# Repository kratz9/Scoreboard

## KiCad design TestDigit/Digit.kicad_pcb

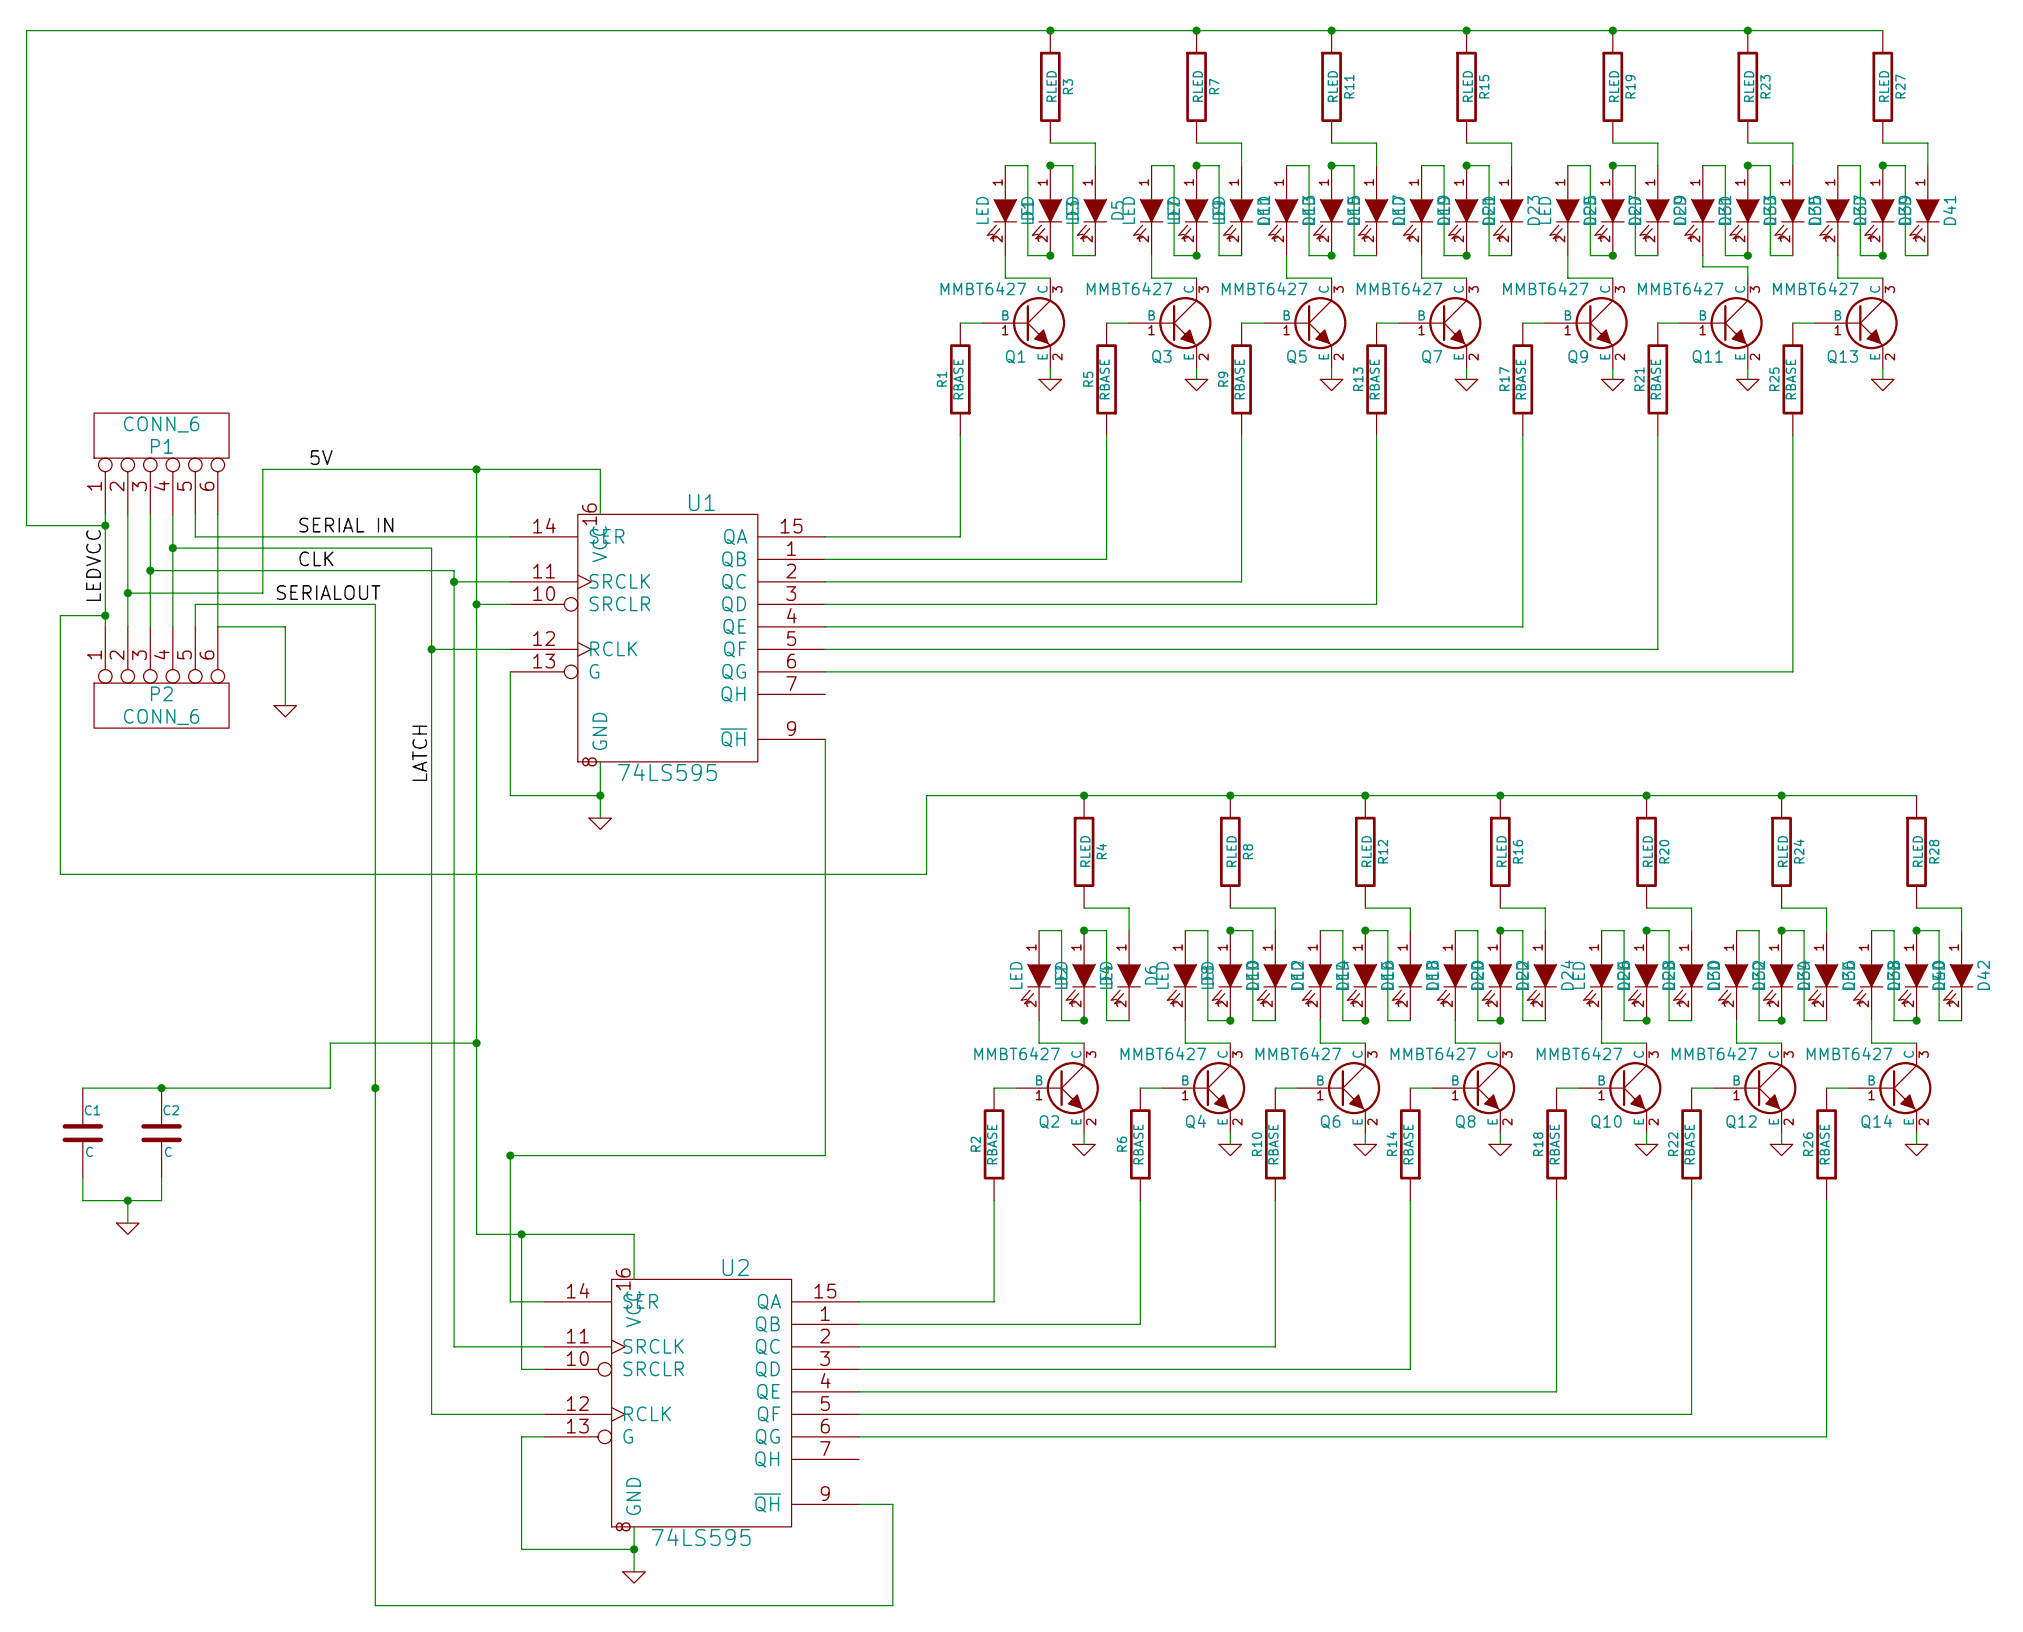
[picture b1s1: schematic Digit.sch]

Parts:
C1, C2: C
D1, D2, D3, D4, D5, D6, D7, D8, D9, D10, D11, D12, D13, D14, D15, D16, D17, D18, D19, D20, D21, D22, D23, D24, D25, D26, D27, D28, D29, D30, D31, D32, D33, D34, D35, D36, D37, D38, D39, D40, D41, D42: LED
P1, P2: CONN_6
Q1, Q2, Q3, Q4, Q5, Q6, Q7, Q8, Q9, Q10, Q11, Q12, Q13, Q14: MMBT6427
R1, R2, R5, R6, R9, R10, R13, R14, R17, R18, R21, R22, R25, R26: RBASE
R3, R4, R7, R8, R11, R12, R15, R16, R19, R20, R23, R24, R27, R28: RLED
U1, U2: 74LS595

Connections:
/5V: C1.1, C2.1, P1.2, P2.2, U1.10 (SRCLR), U1.16 (VCC), U2.10 (SRCLR), U2.16 (VCC)
/CLK: P1.3, P2.3, U1.11 (SRCLK), U2.11 (SRCLK)
/LATCH: P1.4, P2.4, U1.12 (RCLK), U2.12 (RCLK)
/LEDVCC: P1.1, P2.1, R3.1, R4.1, R7.1, R8.1, R11.1, R12.1, R15.1, R16.1, R19.1, R20.1, R23.1, R24.1, R27.1, R28.1
/SERIAL IN: P1.5, U1.14 (SER)
/SERIALOUT: P2.5, U2.9 (~QH)
GND: C1.2, C2.2, P1.6, P2.6, Q1.2 (E), Q2.2 (E), Q3.2 (E), Q4.2 (E), Q5.2 (E), Q6.2 (E), Q7.2 (E), Q8.2 (E), Q9.2 (E), Q10.2 (E), Q11.2 (E), Q12.2 (E), Q13.2 (E), Q14.2 (E), U1.8 (GND), U1.13 (G), U2.8 (GND), U2.13 (G)
unnamed: U1.9 (~QH), U2.14 (SER)
unnamed: D33.1 (A), D35.2 (K)
unnamed: D39.1 (A), D41.2 (K)
unnamed: Q2.1 (B), R2.2
unnamed: Q4.1 (B), R6.2
unnamed: Q6.1 (B), R10.2
unnamed: Q8.1 (B), R14.2
unnamed: D3.1 (A), D5.2 (K)
unnamed: R13.1, U1.3 (QD)
unnamed: R17.1, U1.4 (QE)
unnamed: R21.1, U1.5 (QF)
unnamed: R25.1, U1.6 (QG)
unnamed: Q10.1 (B), R18.2
unnamed: D7.1 (A), D9.2 (K)
unnamed: D9.1 (A), D11.2 (K)
unnamed: D15.1 (A), D17.2 (K)
unnamed: D21.1 (A), D23.2 (K)
unnamed: D27.1 (A), D29.2 (K)
unnamed: D16.1 (A), D18.2 (K)
unnamed: D22.1 (A), D24.2 (K)
unnamed: R26.1, U2.6 (QG)
unnamed: D28.1 (A), D30.2 (K)
unnamed: D34.1 (A), D36.2 (K)
unnamed: D40.1 (A), D42.2 (K)
unnamed: R10.1, U2.2 (QC)
unnamed: Q12.1 (B), R22.2
unnamed: Q14.1 (B), R26.2
unnamed: R2.1, U2.15 (QA)
unnamed: R6.1, U2.1 (QB)
unnamed: R14.1, U2.3 (QD)
unnamed: R18.1, U2.4 (QE)
unnamed: R22.1, U2.5 (QF)
unnamed: D10.1 (A), D12.2 (K)
unnamed: D12.1 (A), R8.2
unnamed: D14.2 (K), Q6.3 (C)
unnamed: D14.1 (A), D16.2 (K)
unnamed: D18.1 (A), R12.2
unnamed: D20.2 (K), Q8.3 (C)
unnamed: D20.1 (A), D22.2 (K)
unnamed: D4.1 (A), D6.2 (K)
unnamed: D41.1 (A), R27.2
unnamed: D2.2 (K), Q2.3 (C)
unnamed: D2.1 (A), D4.2 (K)
unnamed: D6.1 (A), R4.2
unnamed: D8.2 (K), Q4.3 (C)
unnamed: D8.1 (A), D10.2 (K)
unnamed: D38.2 (K), Q14.3 (C)
unnamed: D32.1 (A), D34.2 (K)
unnamed: D36.1 (A), R24.2
unnamed: D38.1 (A), D40.2 (K)
unnamed: D42.1 (A), R28.2
unnamed: D26.1 (A), D28.2 (K)
unnamed: D24.1 (A), R16.2
unnamed: D26.2 (K), Q10.3 (C)
unnamed: D30.1 (A), R20.2
unnamed: D32.2 (K), Q12.3 (C)
unnamed: D13.1 (A), D15.2 (K)
unnamed: D11.1 (A), R7.2
unnamed: D13.2 (K), Q5.3 (C)
unnamed: D17.1 (A), R11.2
unnamed: D19.2 (K), Q7.3 (C)
unnamed: D1.2 (K), Q1.3 (C)
unnamed: D1.1 (A), D3.2 (K)
unnamed: D19.1 (A), D21.2 (K)
unnamed: D5.1 (A), R3.2
unnamed: D7.2 (K), Q3.3 (C)
unnamed: D35.1 (A), R23.2
unnamed: D31.2 (K), Q11.3 (C)
unnamed: D31.1 (A), D33.2 (K)
unnamed: D37.2 (K), Q13.3 (C)
unnamed: D37.1 (A), D39.2 (K)
unnamed: D25.2 (K), Q9.3 (C)
unnamed: D23.1 (A), R15.2
unnamed: D25.1 (A), D27.2 (K)
unnamed: D29.1 (A), R19.2
unnamed: Q3.1 (B), R5.2
unnamed: Q5.1 (B), R9.2
unnamed: R9.1, U1.2 (QC)
unnamed: R1.1, U1.15 (QA)
unnamed: Q1.1 (B), R1.2
unnamed: Q13.1 (B), R25.2
unnamed: Q7.1 (B), R13.2
unnamed: Q9.1 (B), R17.2
unnamed: Q11.1 (B), R21.2
unnamed: R5.1, U1.1 (QB)

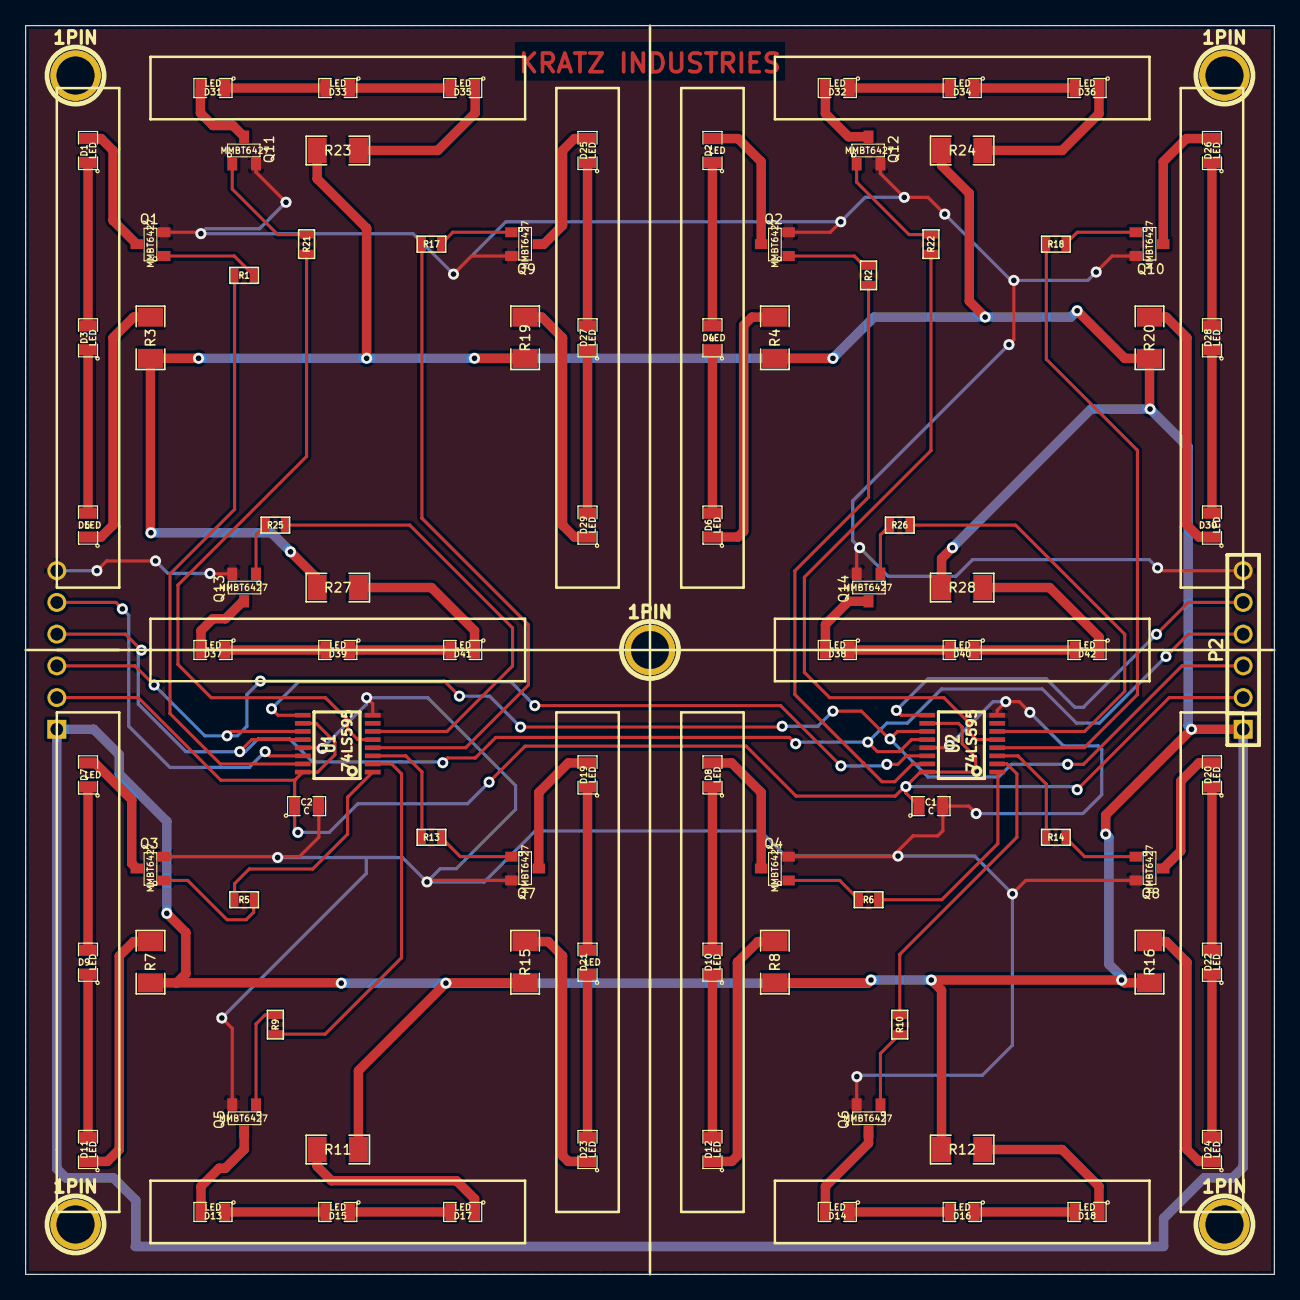
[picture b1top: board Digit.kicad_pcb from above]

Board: 2 copper layers, 100.0 x 100.0 mm, 95 parts (1 on the bottom side), 92 nets.

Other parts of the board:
1PIN, 1PIN#2, 1PIN#3, 1PIN#4, 1PIN#5: P***; 1pin

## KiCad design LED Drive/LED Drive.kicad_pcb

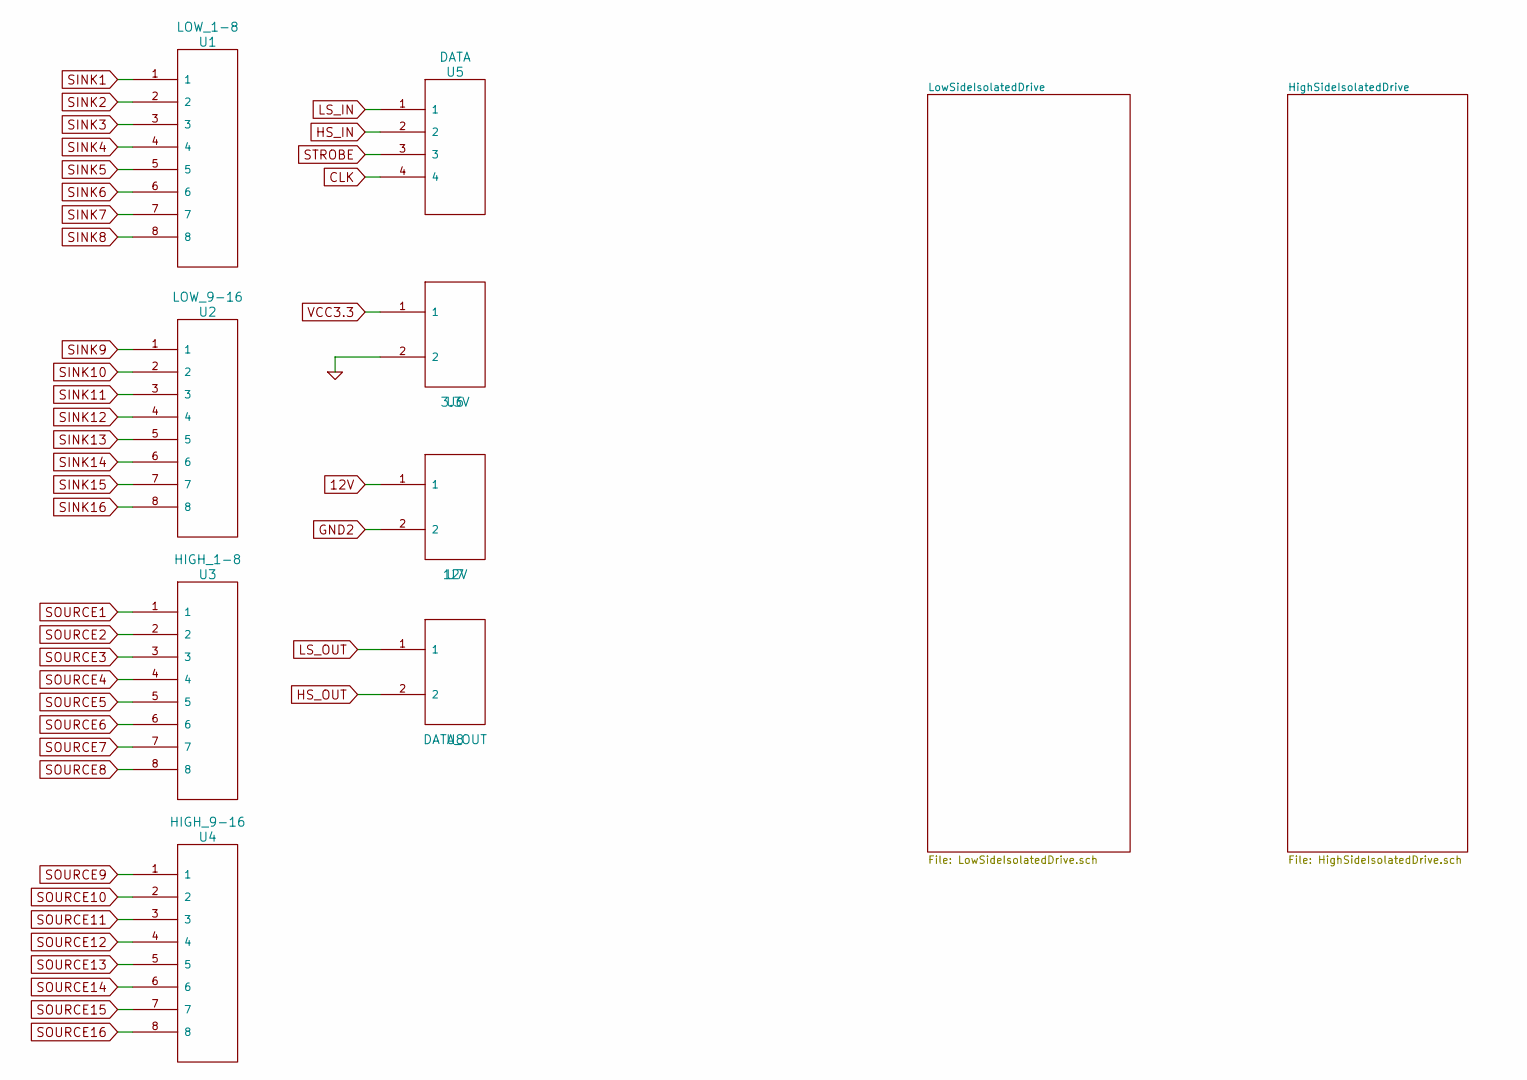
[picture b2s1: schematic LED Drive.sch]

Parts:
U1: LOW_1-8
U2: LOW_9-16
U3: HIGH_1-8
U4: HIGH_9-16
U5: DATA
U6: 3.3V
U7: 12V
U8: DATA_OUT

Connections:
12V: U7.1; also elsewhere on the board
CLK: U5.4; also elsewhere on the board
GND: U6.2; also elsewhere on the board
GND2: U7.2; also elsewhere on the board
HS_IN: U5.2; also elsewhere on the board
HS_OUT: U8.2; also elsewhere on the board
LS_IN: U5.1; also elsewhere on the board
LS_OUT: U8.1; also elsewhere on the board
SINK1: U1.1; also elsewhere on the board
SINK2: U1.2; also elsewhere on the board
SINK3: U1.3; also elsewhere on the board
SINK4: U1.4; also elsewhere on the board
SINK5: U1.5; also elsewhere on the board
SINK6: U1.6; also elsewhere on the board
SINK7: U1.7; also elsewhere on the board
SINK8: U1.8; also elsewhere on the board
SINK9: U2.1; also elsewhere on the board
SINK10: U2.2; also elsewhere on the board
SINK11: U2.3; also elsewhere on the board
SINK12: U2.4; also elsewhere on the board
SINK13: U2.5; also elsewhere on the board
SINK14: U2.6; also elsewhere on the board
SINK15: U2.7; also elsewhere on the board
SINK16: U2.8; also elsewhere on the board
SOURCE1: U3.1; also elsewhere on the board
SOURCE2: U3.2; also elsewhere on the board
SOURCE3: U3.3; also elsewhere on the board
SOURCE4: U3.4; also elsewhere on the board
SOURCE5: U3.5; also elsewhere on the board
SOURCE6: U3.6; also elsewhere on the board
SOURCE7: U3.7; also elsewhere on the board
SOURCE8: U3.8; also elsewhere on the board
SOURCE9: U4.1; also elsewhere on the board
SOURCE10: U4.2; also elsewhere on the board
SOURCE11: U4.3; also elsewhere on the board
SOURCE12: U4.4; also elsewhere on the board
SOURCE13: U4.5; also elsewhere on the board
SOURCE14: U4.6; also elsewhere on the board
SOURCE15: U4.7; also elsewhere on the board
SOURCE16: U4.8; also elsewhere on the board
STROBE: U5.3; also elsewhere on the board
VCC3.3: U6.1; also elsewhere on the board

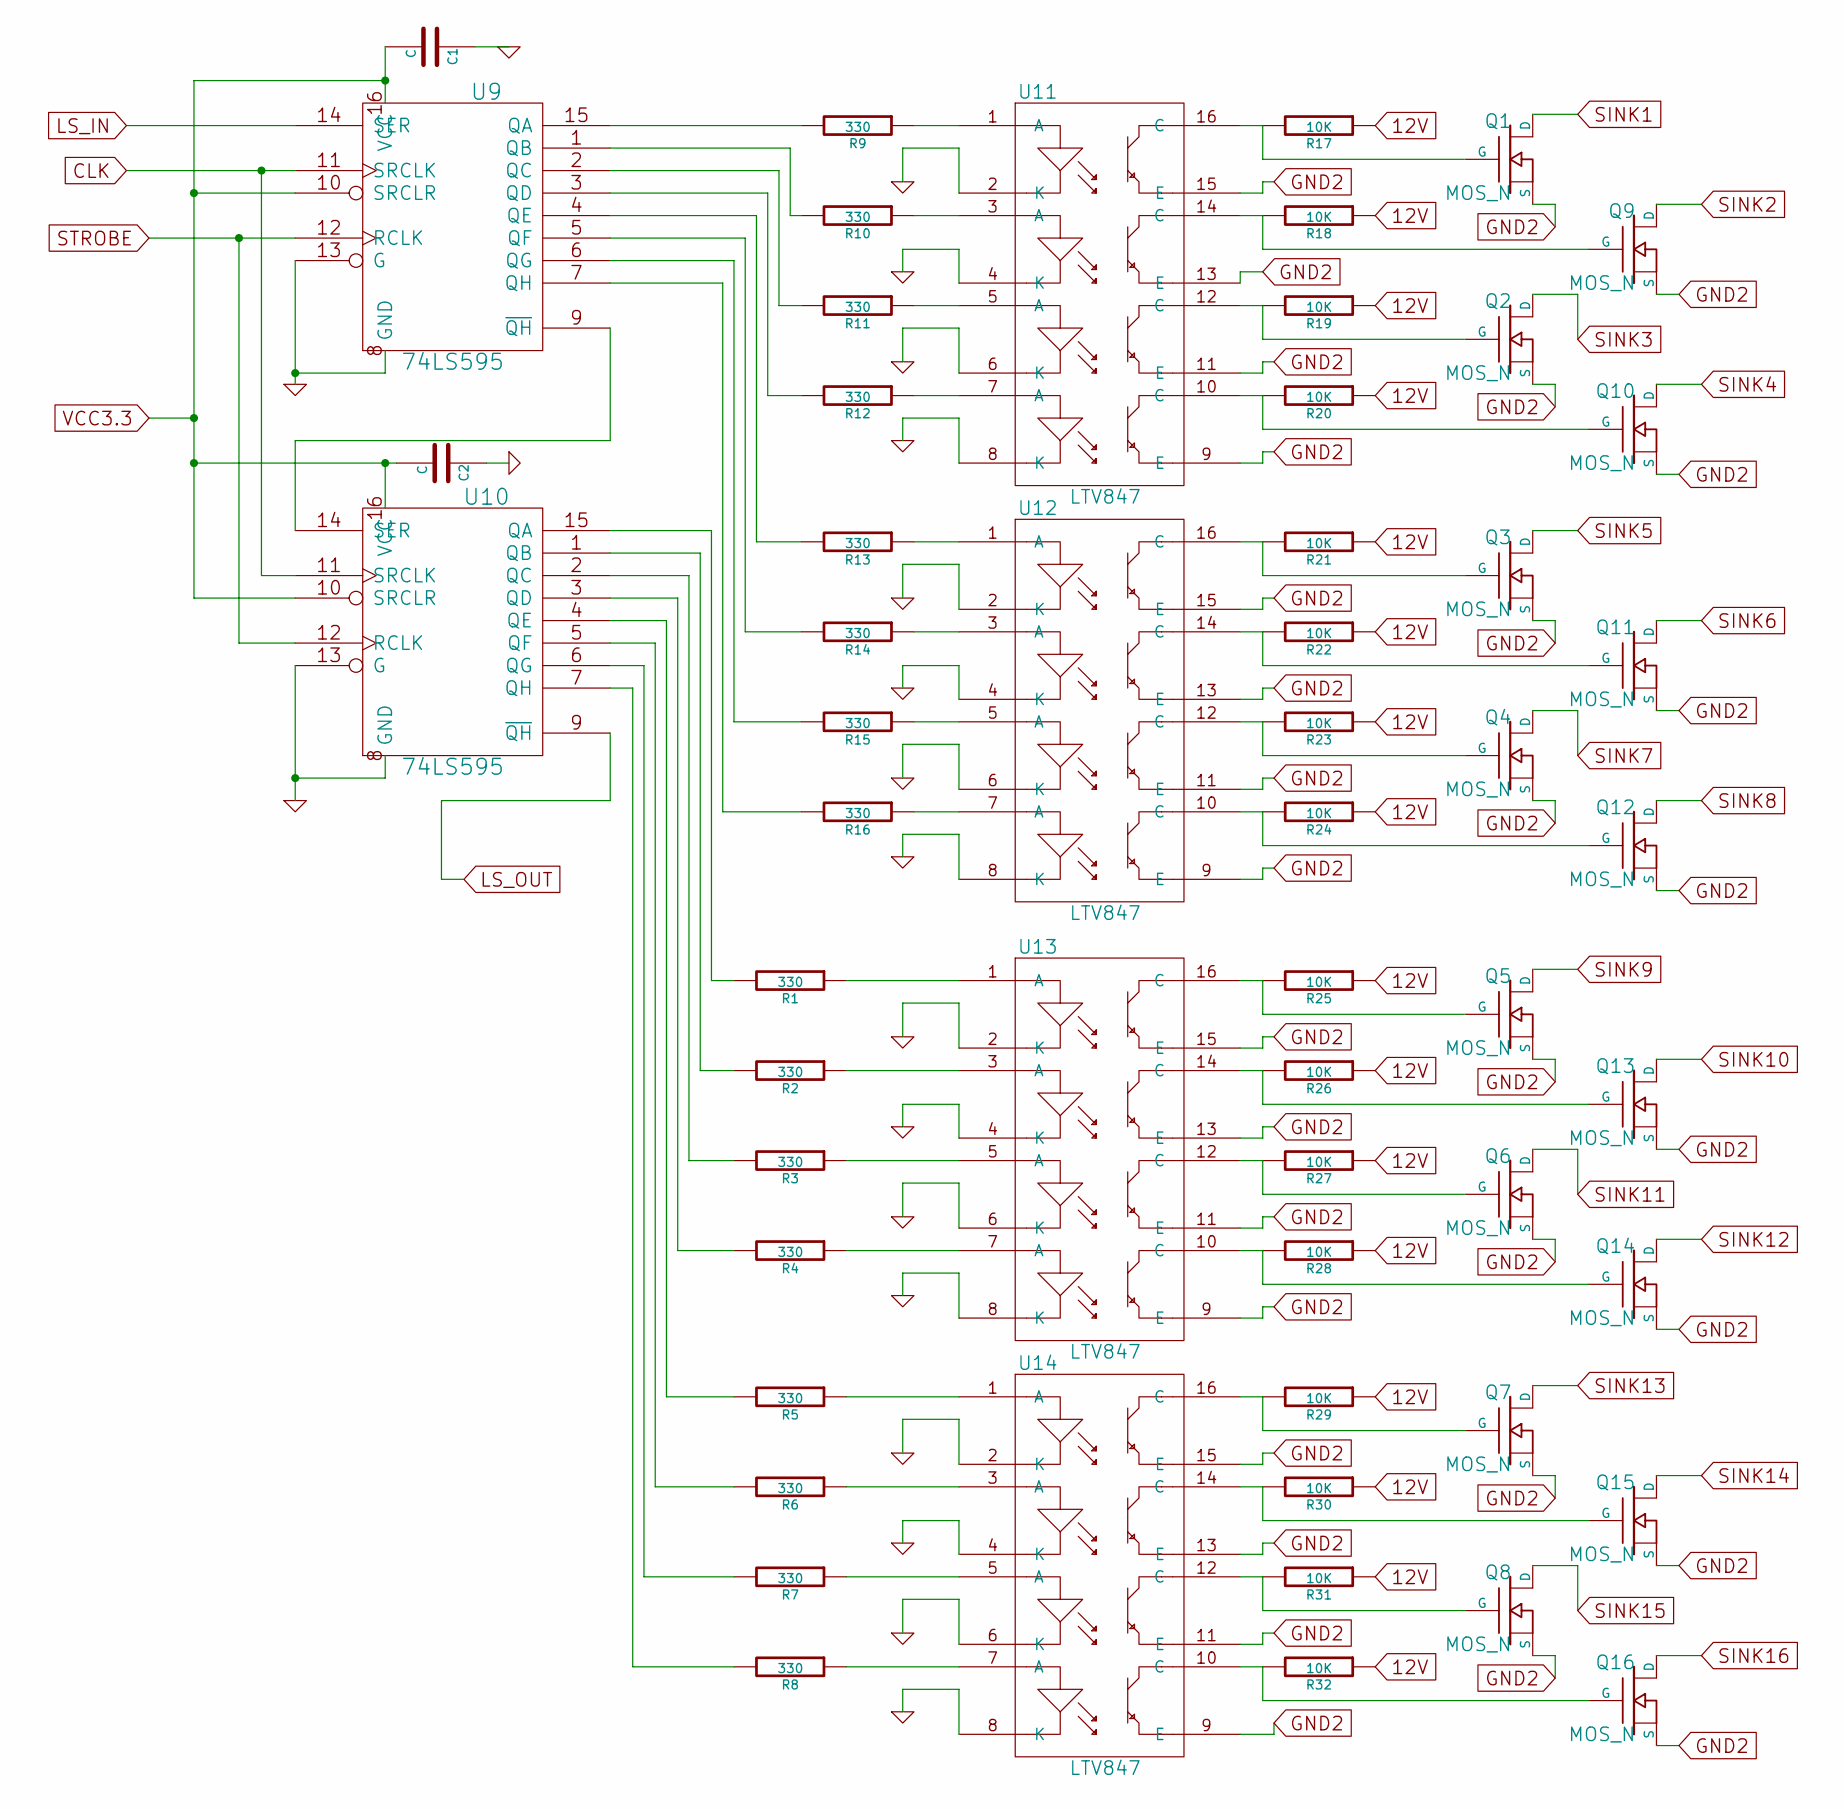
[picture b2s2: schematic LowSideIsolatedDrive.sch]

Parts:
C1, C2: C
Q1, Q2, Q3, Q4, Q5, Q6, Q7, Q8, Q9, Q10, Q11, Q12, Q13, Q14, Q15, Q16: MOS_N
R1, R2, R3, R4, R5, R6, R7, R8, R9, R10, R11, R12, R13, R14, R15, R16: 330
R17, R18, R19, R20, R21, R22, R23, R24, R25, R26, R27, R28, R29, R30, R31, R32: 10K
U9, U10: 74LS595
U11, U12, U13, U14: LTV847

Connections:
12V: R17.1, R18.1, R19.1, R20.1, R21.1, R22.1, R23.1, R24.1, R25.1, R26.1, R27.1, R28.1, R29.1, R30.1, R31.1, R32.1; also elsewhere on the board
CLK: U9.11 (SRCLK), U10.11 (SRCLK); also elsewhere on the board
GND: C1.1, C2.1, U9.8 (GND), U9.13 (G), U10.8 (GND), U10.13 (G), U11.2 (K), U11.4 (K), U11.6 (K), U11.8 (K), U12.2 (K), U12.4 (K), U12.6 (K), U12.8 (K), U13.2 (K), U13.4 (K), U13.6 (K), U13.8 (K), U14.2 (K), U14.4 (K), U14.6 (K), U14.8 (K); also elsewhere on the board
GND2: Q1.S, Q2.S, Q3.S, Q4.S, Q5.S, Q6.S, Q7.S, Q8.S, Q9.S, Q10.S, Q11.S, Q12.S, Q13.S, Q14.S, Q15.S, Q16.S, U11.9 (E), U11.11 (E), U11.13 (E), U11.15 (E), U12.9 (E), U12.11 (E), U12.13 (E), U12.15 (E), U13.9 (E), U13.11 (E), U13.13 (E), U13.15 (E), U14.9 (E), U14.11 (E), U14.13 (E), U14.15 (E); also elsewhere on the board
LS_IN: U9.14 (SER); also elsewhere on the board
LS_OUT: U10.9 (~QH); also elsewhere on the board
unnamed: Q13.G, R26.2, U13.14 (C)
unnamed: Q5.G, R25.2, U13.16 (C)
unnamed: R9.2, U9.15 (QA)
unnamed: Q4.G, R23.2, U12.12 (C)
unnamed: Q12.G, R24.2, U12.10 (C)
unnamed: R1.1, U13.1 (A)
unnamed: R2.1, U13.3 (A)
unnamed: R3.1, U13.5 (A)
unnamed: R4.1, U13.7 (A)
unnamed: Q7.G, R29.2, U14.16 (C)
unnamed: Q6.G, R27.2, U13.12 (C)
unnamed: Q14.G, R28.2, U13.10 (C)
unnamed: R5.1, U14.1 (A)
unnamed: R6.1, U14.3 (A)
unnamed: R7.1, U14.5 (A)
unnamed: R8.1, U14.7 (A)
unnamed: R12.2, U9.3 (QD)
unnamed: Q1.G, R17.2, U11.16 (C)
unnamed: Q9.G, R18.2, U11.14 (C)
unnamed: Q2.G, R19.2, U11.12 (C)
unnamed: R10.2, U9.1 (QB)
unnamed: R11.2, U9.2 (QC)
unnamed: Q3.G, R21.2, U12.16 (C)
unnamed: Q11.G, R22.2, U12.14 (C)
unnamed: R14.1, U12.3 (A)
unnamed: Q10.G, R20.2, U11.10 (C)
unnamed: R13.1, U12.1 (A)
unnamed: R15.1, U12.5 (A)
unnamed: R16.1, U12.7 (A)
unnamed: R13.2, U9.4 (QE)
unnamed: R14.2, U9.5 (QF)
unnamed: R15.2, U9.6 (QG)
unnamed: R16.2, U9.7 (QH)
unnamed: R1.2, U10.15 (QA)
unnamed: R2.2, U10.1 (QB)
unnamed: R3.2, U10.2 (QC)
unnamed: Q8.G, R31.2, U14.12 (C)
unnamed: Q15.G, R30.2, U14.14 (C)
unnamed: Q16.G, R32.2, U14.10 (C)
unnamed: R7.2, U10.6 (QG)
unnamed: R4.2, U10.3 (QD)
unnamed: R5.2, U10.4 (QE)
unnamed: R6.2, U10.5 (QF)
unnamed: R8.2, U10.7 (QH)
unnamed: U9.9 (~QH), U10.14 (SER)
unnamed: R12.1, U11.7 (A)
unnamed: R9.1, U11.1 (A)
unnamed: R10.1, U11.3 (A)
unnamed: R11.1, U11.5 (A)
SINK1: Q1.D; also elsewhere on the board
SINK2: Q9.D; also elsewhere on the board
SINK3: Q2.D; also elsewhere on the board
SINK4: Q10.D; also elsewhere on the board
SINK5: Q3.D; also elsewhere on the board
SINK6: Q11.D; also elsewhere on the board
SINK7: Q4.D; also elsewhere on the board
SINK8: Q12.D; also elsewhere on the board
SINK9: Q5.D; also elsewhere on the board
SINK10: Q13.D; also elsewhere on the board
SINK11: Q6.D; also elsewhere on the board
SINK12: Q14.D; also elsewhere on the board
SINK13: Q7.D; also elsewhere on the board
SINK14: Q15.D; also elsewhere on the board
SINK15: Q8.D; also elsewhere on the board
SINK16: Q16.D; also elsewhere on the board
STROBE: U9.12 (RCLK), U10.12 (RCLK); also elsewhere on the board
VCC3.3: C1.2, C2.2, U9.10 (SRCLR), U9.16 (VCC), U10.10 (SRCLR), U10.16 (VCC); also elsewhere on the board

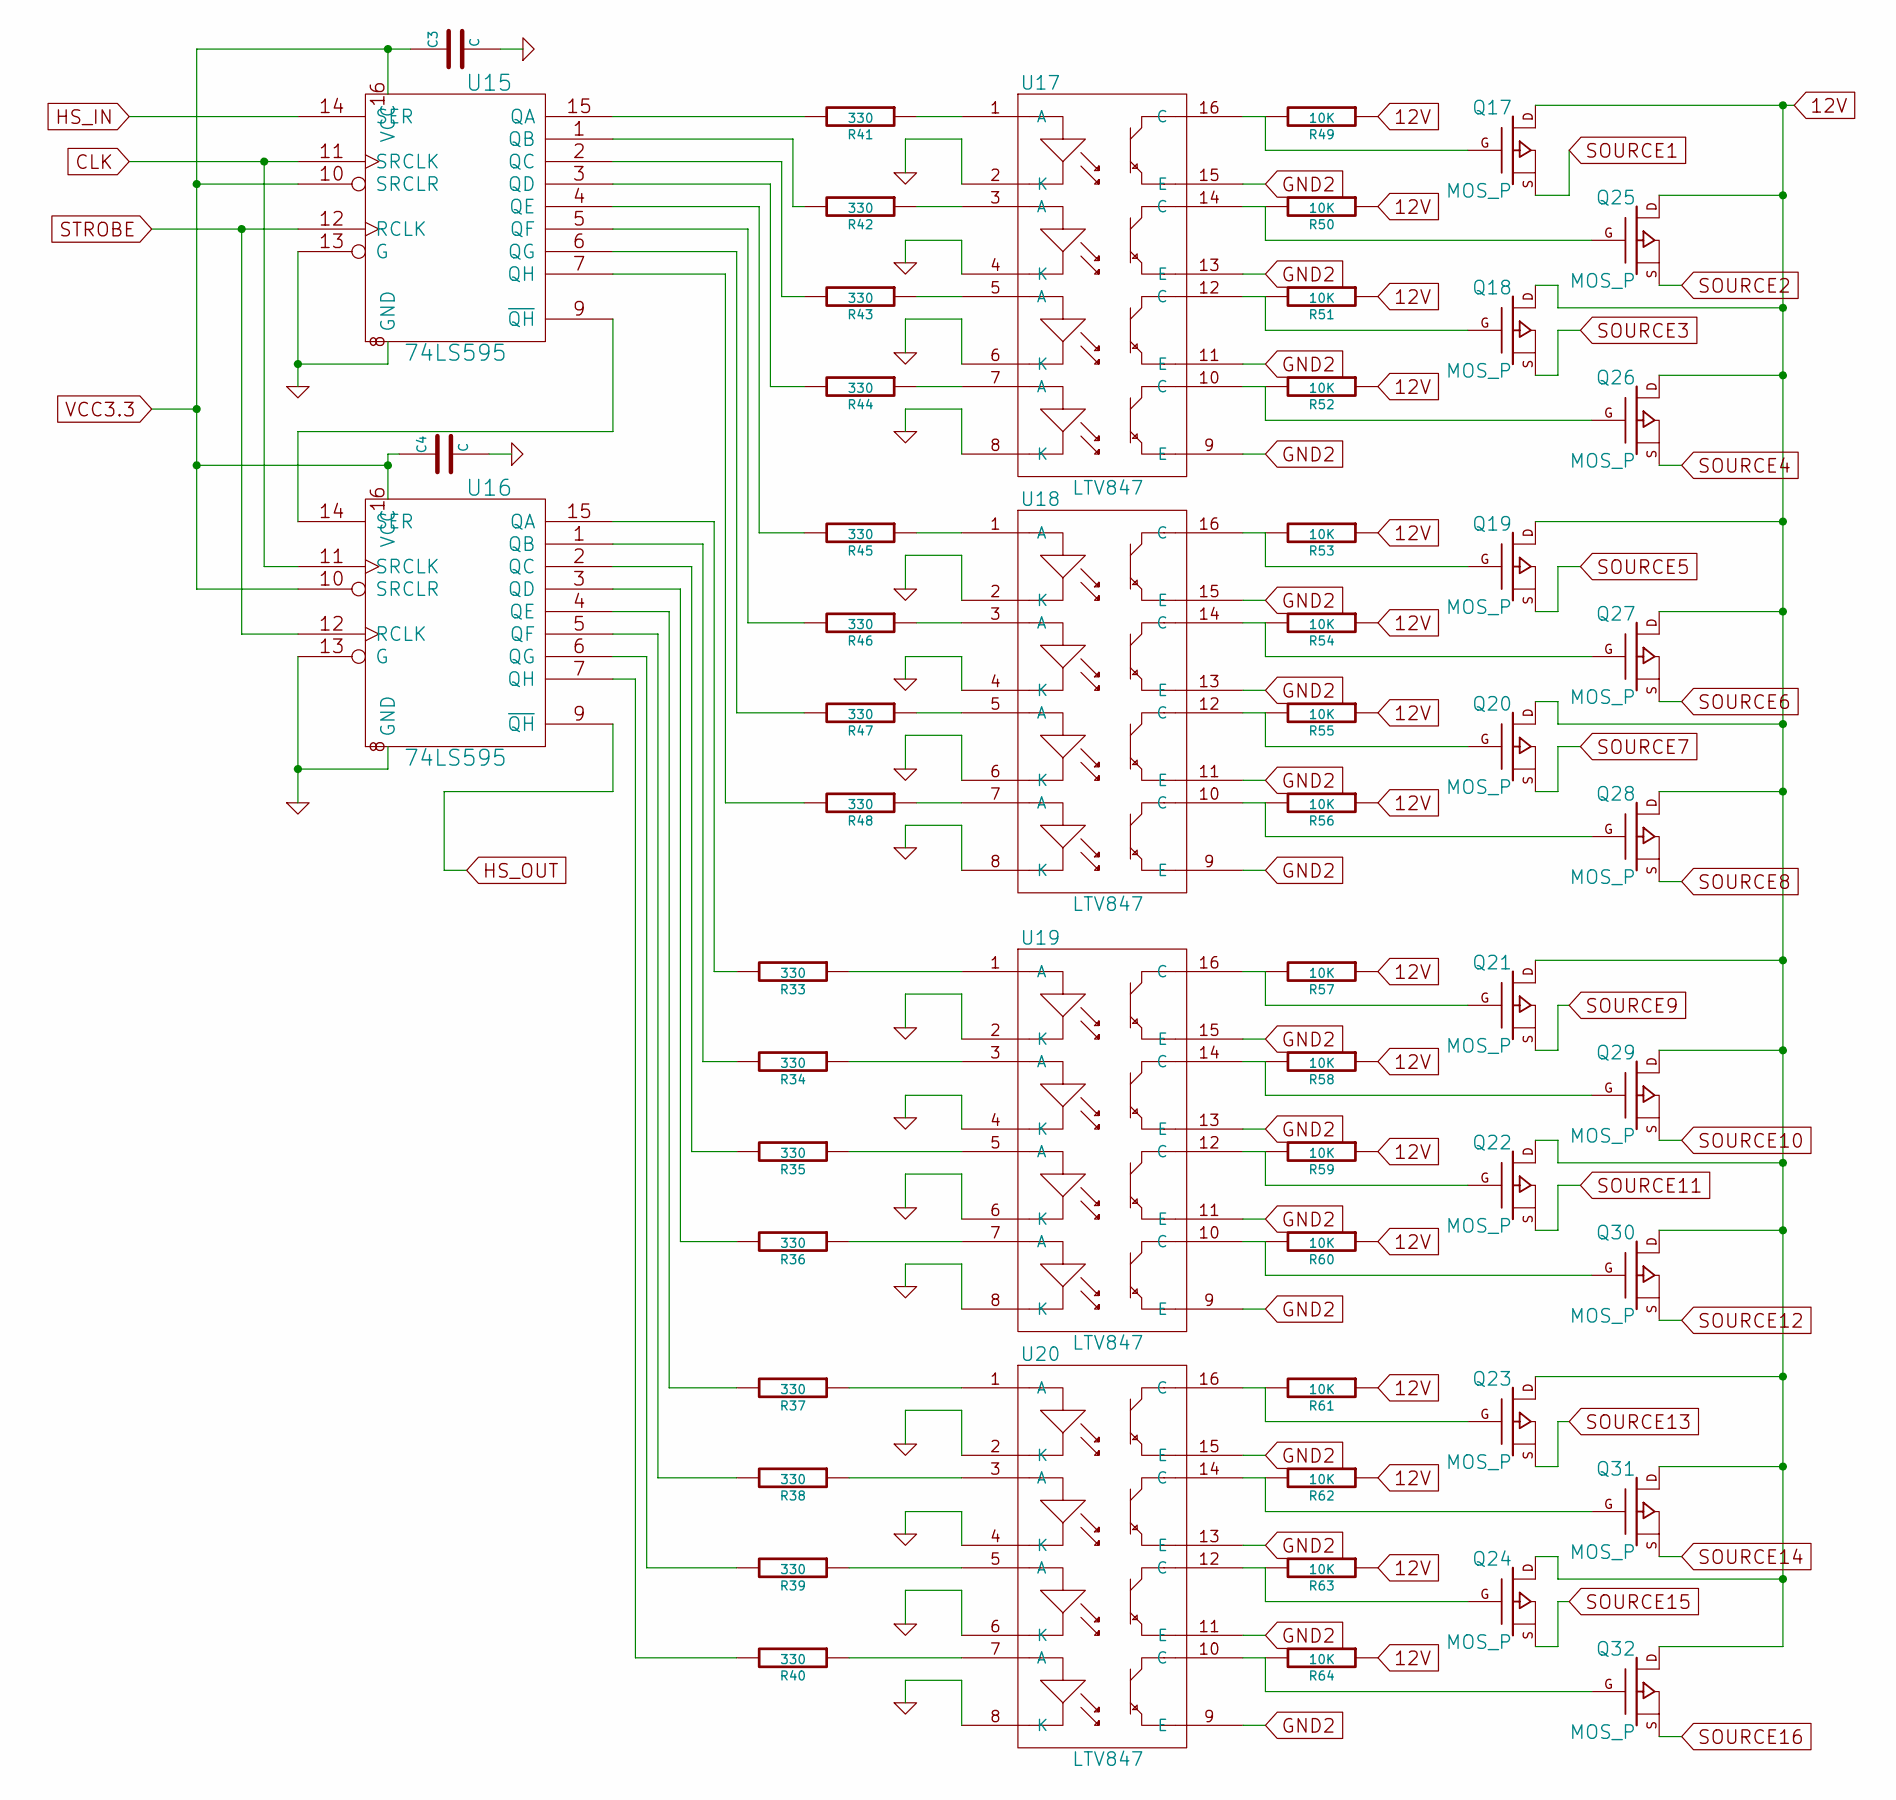
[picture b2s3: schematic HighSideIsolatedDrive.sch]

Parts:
C3, C4: C
Q17, Q18, Q19, Q20, Q21, Q22, Q23, Q24, Q25, Q26, Q27, Q28, Q29, Q30, Q31, Q32: MOS_P
R33, R34, R35, R36, R37, R38, R39, R40, R41, R42, R43, R44, R45, R46, R47, R48: 330
R49, R50, R51, R52, R53, R54, R55, R56, R57, R58, R59, R60, R61, R62, R63, R64: 10K
U15, U16: 74LS595
U17, U18, U19, U20: LTV847

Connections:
12V: Q17.D, Q18.D, Q19.D, Q20.D, Q21.D, Q22.D, Q23.D, Q24.D, Q25.D, Q26.D, Q27.D, Q28.D, Q29.D, Q30.D, Q31.D, Q32.D, R49.1, R50.1, R51.1, R52.1, R53.1, R54.1, R55.1, R56.1, R57.1, R58.1, R59.1, R60.1, R61.1, R62.1, R63.1, R64.1; also elsewhere on the board
CLK: U15.11 (SRCLK), U16.11 (SRCLK); also elsewhere on the board
GND: C3.2, C4.2, U15.8 (GND), U15.13 (G), U16.8 (GND), U16.13 (G), U17.2 (K), U17.4 (K), U17.6 (K), U17.8 (K), U18.2 (K), U18.4 (K), U18.6 (K), U18.8 (K), U19.2 (K), U19.4 (K), U19.6 (K), U19.8 (K), U20.2 (K), U20.4 (K), U20.6 (K), U20.8 (K); also elsewhere on the board
GND2: U17.9 (E), U17.11 (E), U17.13 (E), U17.15 (E), U18.9 (E), U18.11 (E), U18.13 (E), U18.15 (E), U19.9 (E), U19.11 (E), U19.13 (E), U19.15 (E), U20.9 (E), U20.11 (E), U20.13 (E), U20.15 (E); also elsewhere on the board
HS_IN: U15.14 (SER); also elsewhere on the board
HS_OUT: U16.9 (~QH); also elsewhere on the board
unnamed: Q23.G, R61.2, U20.16 (C)
unnamed: Q31.G, R62.2, U20.14 (C)
unnamed: Q22.G, R59.2, U19.12 (C)
unnamed: Q30.G, R60.2, U19.10 (C)
unnamed: R37.1, U20.1 (A)
unnamed: R38.1, U20.3 (A)
unnamed: R39.1, U20.5 (A)
unnamed: R40.1, U20.7 (A)
unnamed: R34.2, U16.1 (QB)
unnamed: R47.2, U15.6 (QG)
unnamed: R48.2, U15.7 (QH)
unnamed: R33.2, U16.15 (QA)
unnamed: R35.2, U16.2 (QC)
unnamed: R36.2, U16.3 (QD)
unnamed: Q32.G, R64.2, U20.10 (C)
unnamed: Q24.G, R63.2, U20.12 (C)
unnamed: R45.2, U15.4 (QE)
unnamed: R46.2, U15.5 (QF)
unnamed: Q19.G, R53.2, U18.16 (C)
unnamed: Q27.G, R54.2, U18.14 (C)
unnamed: R48.1, U18.7 (A)
unnamed: R45.1, U18.1 (A)
unnamed: R46.1, U18.3 (A)
unnamed: R47.1, U18.5 (A)
unnamed: Q20.G, R55.2, U18.12 (C)
unnamed: Q21.G, R57.2, U19.16 (C)
unnamed: Q29.G, R58.2, U19.14 (C)
unnamed: R34.1, U19.3 (A)
unnamed: Q28.G, R56.2, U18.10 (C)
unnamed: R33.1, U19.1 (A)
unnamed: R35.1, U19.5 (A)
unnamed: R36.1, U19.7 (A)
unnamed: Q25.G, R50.2, U17.14 (C)
unnamed: Q18.G, R51.2, U17.12 (C)
unnamed: R40.2, U16.7 (QH)
unnamed: R37.2, U16.4 (QE)
unnamed: R38.2, U16.5 (QF)
unnamed: R39.2, U16.6 (QG)
unnamed: Q17.G, R49.2, U17.16 (C)
unnamed: U15.9 (~QH), U16.14 (SER)
unnamed: Q26.G, R52.2, U17.10 (C)
unnamed: R41.1, U17.1 (A)
unnamed: R41.2, U15.15 (QA)
unnamed: R42.1, U17.3 (A)
unnamed: R42.2, U15.1 (QB)
unnamed: R43.1, U17.5 (A)
unnamed: R43.2, U15.2 (QC)
unnamed: R44.1, U17.7 (A)
unnamed: R44.2, U15.3 (QD)
SOURCE1: Q17.S; also elsewhere on the board
SOURCE2: Q25.S; also elsewhere on the board
SOURCE3: Q18.S; also elsewhere on the board
SOURCE4: Q26.S; also elsewhere on the board
SOURCE5: Q19.S; also elsewhere on the board
SOURCE6: Q27.S; also elsewhere on the board
SOURCE7: Q20.S; also elsewhere on the board
SOURCE8: Q28.S; also elsewhere on the board
SOURCE9: Q21.S; also elsewhere on the board
SOURCE10: Q29.S; also elsewhere on the board
SOURCE11: Q22.S; also elsewhere on the board
SOURCE12: Q30.S; also elsewhere on the board
SOURCE13: Q23.S; also elsewhere on the board
SOURCE14: Q31.S; also elsewhere on the board
SOURCE15: Q24.S; also elsewhere on the board
SOURCE16: Q32.S; also elsewhere on the board
STROBE: U15.12 (RCLK), U16.12 (RCLK); also elsewhere on the board
VCC3.3: C3.1, C4.1, U15.10 (SRCLR), U15.16 (VCC), U16.10 (SRCLR), U16.16 (VCC); also elsewhere on the board

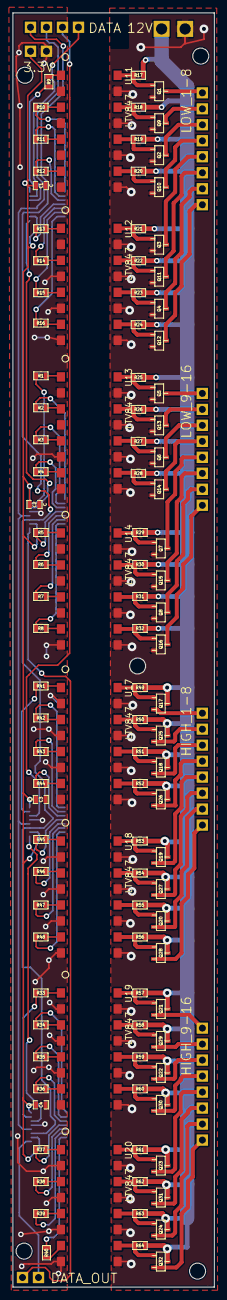
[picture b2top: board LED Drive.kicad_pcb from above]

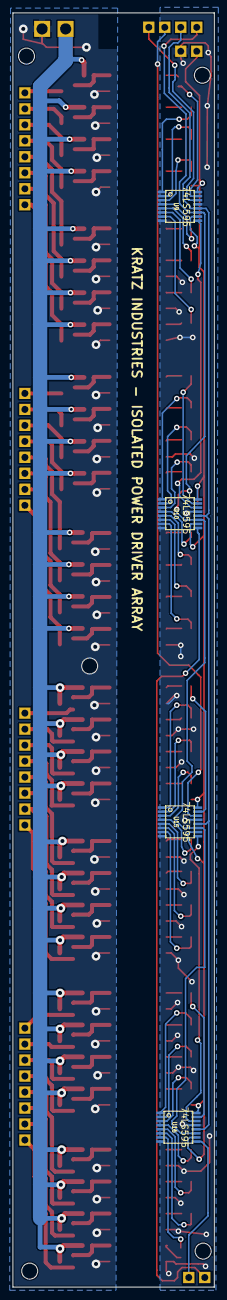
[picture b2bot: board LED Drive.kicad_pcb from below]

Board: 2 copper layers, 32.0 x 202.4 mm, 125 parts (4 on the bottom side), 140 nets.

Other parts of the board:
HOLE: VAL**; HOLE
HOLE#2, HOLE#3, HOLE#4, HOLE#5: VAL**; HOLE
